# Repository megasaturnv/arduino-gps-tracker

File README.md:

# arduino-gps-tracker
## Synopsis
An Arduino-based GPS tracking solution. One Arduino and Ublox Neo-6m (GY-NEO6MV2) GPS module on stripboard / veroboard is used as the GPS tracking device. The other is an Arduino handheld controller which requests information from the tracking device and displays the coordinates, GPS location and location on a map. By default, the display is a 128x160 1.8" TFT LCD but the code can be adapted for other displays. Communication occurs between the two devices with the HC-12 wireless serial communication module. This project can be adapted to use other methods of wireless communication such as the XBee or GSM mobile network. Please make sure the frequency used and transmitting power is legal in your country.

## Description of Arduino handheld controller
The Arduino handheld controller is used by a user to find the location of their GPS tracking device. It is powered by an 18650 Li-ion cell and consists of Li-ion protection and charging circuitry, an Arduino, a 1.8" TFT LCD display, a HC-12 wireless communication module and buttons for requesting various data from the tracking device. When it receives data from the tracking device, the Arduino will interpret the message formtted as \<datatype>:\<CSV of data> into \<data type> and an array of data for each item in \<CSV of data>. Then, the tracker respond in the appropriate way. The messages it understands and the way it responds are listed below:

#### if receive "volts:\[millivolts\]"
Display the tracking device Arduino's VCC voltage on the 1.8" TFT LCD display.

#### if receive "gps:\<latitude>, \<longitude>, \<num of satellites>, \<accuracy>, \<speed>, \<direction>, \<age of data>, \<checksum>"
Display these figures on the 1.8" TFT LCD display.

### Buttons
The buttons on the handheld controller are pulled high by the Arduino's internal pull-up resistors. To activate the button, the pin should be connected to ground. 

### The Arduino pins used to connect to peripherals is shown below:
#define name | Pin no. | Function
--- | --- | ---
SOFTWARE_SERIAL_TX | 2 | For the HC-12 module. Connects to HC-12 RX
SOFTWARE_SERIAL_RX | 3 | For the HC-12 module. Connects to HC-12 TX
CELLVOLTS_BUTTON | 4 | Push button connected to ground. transmit: "cell:volts" to the tracking device
REQUEST_GPS_ONCE_BUTTON | 5 | Push button connected to ground. transmit: "gps:once"
REQUEST_GPS_CONTINUOUS_BUTTON | 6 | Push button connected to ground. transmit: "gps:continuous"
REQUEST_GPS_STOP_BUTTON | 7 | Push button connected to ground. transmit: "gps:stop"
sclk | 13 | Connection to 1.8" TFT LCD screen. Connects to TFT SCK/
mosi | 11 | Connection to 1.8" TFT LCD screen. Connects to TFT SDA/
cs | 10 | Connection to 1.8" TFT LCD screen. Connects to TFT SCS/
dc | A0 | Connection to 1.8" TFT LCD screen. Connects to TFT A0/
rst | A1 | Connection to 1.8" TFT LCD screen. Connects to TFT RESET/

### Showing location on the display's map
*COMING SOON*

### How to create your own maps for the TFT LCD screen
*COMING SOON*

## Description of Arduino GPS tracking device
The Arduino tracking device should be attached to an object which the user wants to track. It is powered by an 18650 Li-ion cell and consists of Li-ion protection and charging circuitry, an Arduino, a Ublox Neo-6m (GY-NEO6MV2) GPS module and a HC-12 wireless communication module. The circuit is built onto a piece of stripboard / veroboard. When powered, the Arduino will go into a light sleep mode. It will wake up when it receives serial data from the HC-12 module. The Arduino will interpret the message formtted as \<datatype>:\<CSV of data> into \<data type> and an array of data for each item in \<CSV of data>. Then, the tracker responds in the appropriate way.

### Kicad designs

### The messages the Arduino GPS tracking device understands and the way it responds are listed below:
#### if receive "cell:volts"
send "cell:\[millivolts\]" where millivolts = voltage of the tracking device Arduino's VCC pin

#### if receive "gps:once"
send "message:received gps once" and try to get GPS coordinates. Then, send coordinates once and go to sleep

#### if receive "gps:continuous"
send "message:received gps continuous" and try to get GPS coordinates. Then, send coordinates every 10 seconds

#### if receive "gps:stopcontinuous"
send "message:gpsstopcontinuous" and then stop sending GPS coordinates continuously

If the tracking device is requested for coordinates, it will try and get its GPS location. If it cannot get a fix after GPS_TIMEOUT milliseconds, the Arduino will send "message:Unable to get GPS fix" to the handheld controller, where it will be displayed on the screen. This functionality can be disabled by setting GPS_TIMEOUT to 0 (#define GPS_TIMEOUT 0).

If no more GPS coordinates are required (after a successful GPS lock with "gps:once" or "gps:stopcontinuous" commmand) or if the Arduino has been on for more than MAX_ON_TIME, go to sleep. MAX_ON_TIME is a failsafe to make sure the Arduino doesn't stay on for more than MAX_ON_TIME milliseconds. This functionality can be disabled by setting MAX_ON_TIME to 0 (#define MAX_ON_TIME 0).

### The Arduino pins used to connect to peripherals is shown below:

Pin description | Pin no. | Function
--- | --- | ---
SERIAL_UART_RX | 0 | For the HC-12 module. Connects to HC-12 TX
SERIAL_UART_TX | 1 | For the HC-12 module. Connects to HC-12 RX

#define name | Pin no. | Function
--- | --- | ---
SOFTWARE_SERIAL_RX | 3 | Software serial RX pin, to be connected to the GPS module's TX
SOFTWARE_SERIAL_TX | 2 | Software serial TX pin, to be connected to the GPS module's RX

## Motivation
I have created this project to be used as a dog tracker, but it can easily track a car and other valuable item.

## Installation
Upload gpsTracker_handheldController to the Arduino which will be used in the handheld controller. Upload gpsTracker_trackingDevice to the Arduino which will be used in the tracking device. Follow the build diagrams and create the stripboard / veroboard circuit board from the KiCAD files to construct the GPS tracking device.

## Libraries used
### Handheld controller
* [Adafruit_GFX](https://github.com/adafruit/Adafruit-GFX-Library)
* [Adafruit_QDTech](https://github.com/zigwart/Adafruit_QDTech) Note my display is QDTech 1.8" 128x160 pixel LCD board using a Samsung S6D02A1 chip, so I need a special library.
* [SPI](https://github.com/arduino/Arduino/tree/master/hardware/arduino/avr/libraries/SPI)
* [SoftwareSerial](https://github.com/arduino/Arduino/tree/master/hardware/arduino/avr/libraries/SoftwareSerial)

### Tracking device
* [avr/power](https://github.com/Synapseware/avr/blob/master/include/avr/power.h)
* [avr/sleep](https://github.com/Synapseware/avr/blob/master/include/avr/sleep.h)
* [SoftwareSerial](https://github.com/arduino/Arduino/tree/master/hardware/arduino/avr/libraries/SoftwareSerial)
* [TinyGPS](http://arduiniana.org/libraries/tinygps/)

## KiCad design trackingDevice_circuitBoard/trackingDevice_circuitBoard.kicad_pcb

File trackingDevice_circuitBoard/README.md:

# gpsTracker_trackingDevice_circuitBoard
Schematic and circuit board design for the tracking device. Used to create a stripboard / veroboard circuit board.

To be opened with KiCad EDA, a cross platform, free and open source electronics design automation suite.
* http://kicad-pcb.org/
* https://github.com/kicad

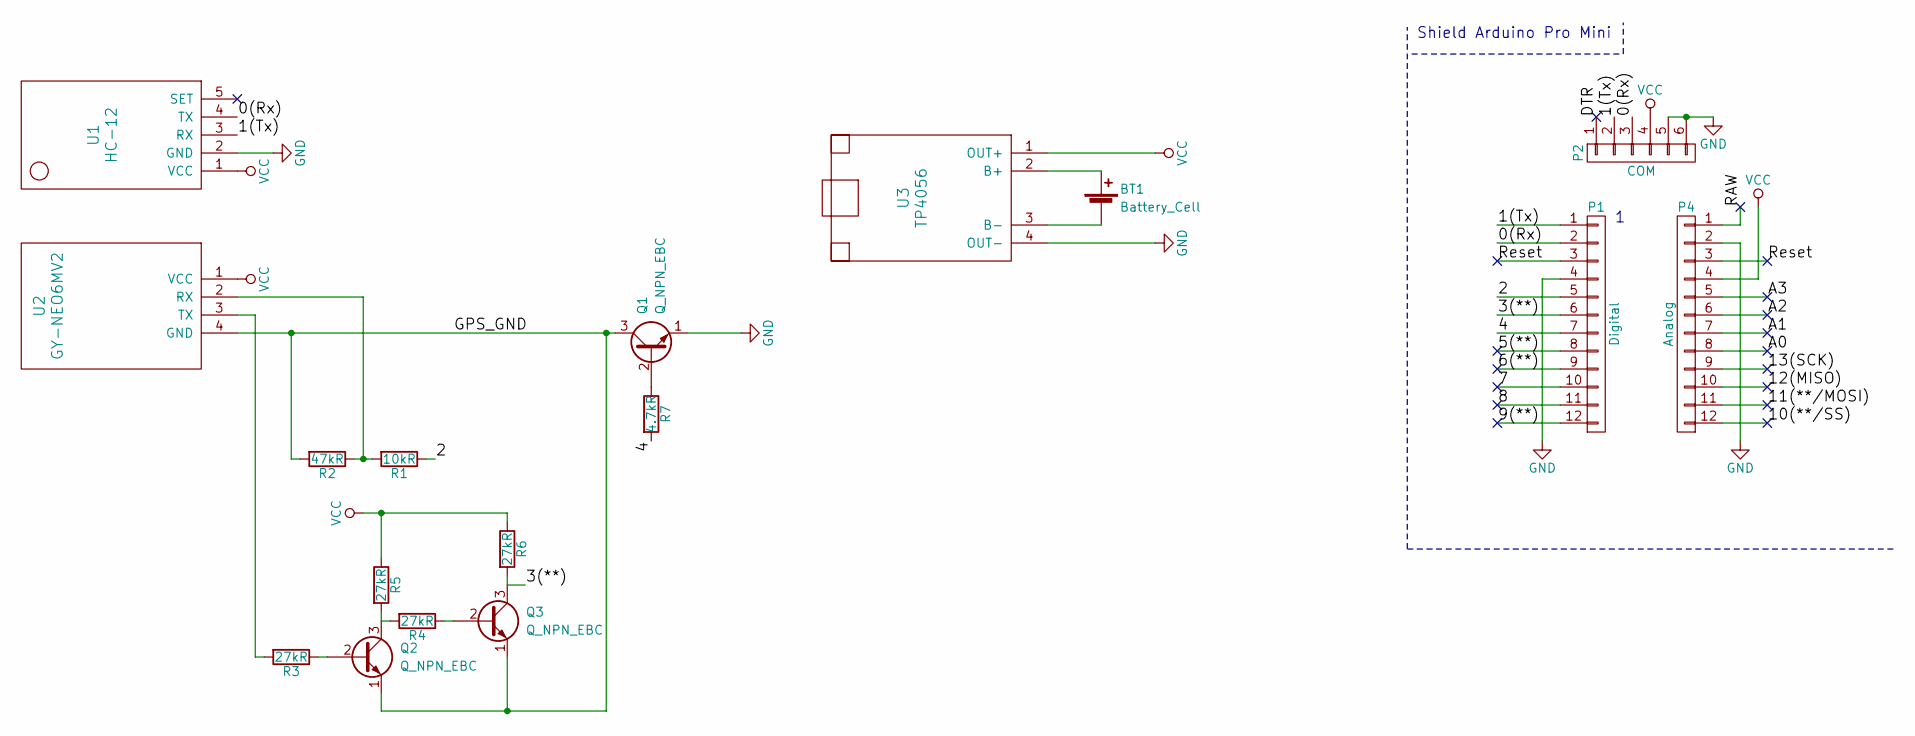
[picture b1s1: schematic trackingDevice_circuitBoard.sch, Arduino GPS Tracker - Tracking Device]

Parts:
BT1: Battery_Cell; CP_Axial_L67.0mm_D23.0mm_P75.00mm_Horizontal
P1: Digital; Socket_Strip_Straight_1x12_Pitch2.54mm
P2: COM
P4: Analog; Socket_Strip_Straight_1x12_Pitch2.54mm
Q1, Q2, Q3: Q_NPN_EBC; TO-92_Inline_Wide
R1: 10kR; R_Axial_DIN0207_L6.3mm_D2.5mm_P10.16mm_Horizontal
R2: 47kR; R_Axial_DIN0207_L6.3mm_D2.5mm_P10.16mm_Horizontal
R3, R4, R5, R6: 27kR; R_Axial_DIN0207_L6.3mm_D2.5mm_P10.16mm_Horizontal
R7: 4.7kR; R_Axial_DIN0207_L6.3mm_D2.5mm_P15.24mm_Horizontal
U1: HC-12; Socket_Strip_Straight_1x05_Pitch2.54mm
U2: GY-NEO6MV2; Socket_Strip_Straight_1x04_Pitch2.54mm
U3: TP4056; TP4056_with_protection

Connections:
/0(Rx): P1.2, P2.3, U1.4 (TX)
/1(Tx): P1.1, P2.2, U1.3 (RX)
/2: P1.5, R1.1
/3(**): P1.6, Q3.3 (C), R6.2
/4: P1.7, R7.2
/5(**): P1.8
/6(**): P1.9
/7: P1.10
/8: P1.11
/9(**): P1.12
/10(**/SS): P4.12
/11(**/MOSI): P4.11
/12(MISO): P4.10
/13(SCK): P4.9
/A0: P4.8
/A1: P4.7
/A2: P4.6
/A3: P4.5
/GPS_GND: Q1.3 (C), Q2.1 (E), Q3.1 (E), R2.2, U2.4 (GND)
/RAW: P4.1
/Reset: P1.3, P4.3
GND: P1.4, P2.5, P2.6, P4.2, Q1.1 (E), U1.2 (GND), U3.4 (OUT-)
unnamed: BT1.1 (+), U3.2 (B+)
unnamed: BT1.2 (-), U3.3 (B-)
unnamed: Q1.2 (B), R7.1
unnamed: Q2.2 (B), R3.1
unnamed: Q2.3 (C), R4.2, R5.2
unnamed: Q3.2 (B), R4.1
unnamed: R1.2, R2.1, U2.2 (RX)
unnamed: R3.2, U2.3 (TX)
VCC: P2.4, P4.4, R5.1, R6.1, U1.1 (VCC), U2.1 (VCC), U3.1 (OUT+)

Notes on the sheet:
Shield Arduino Pro Mini

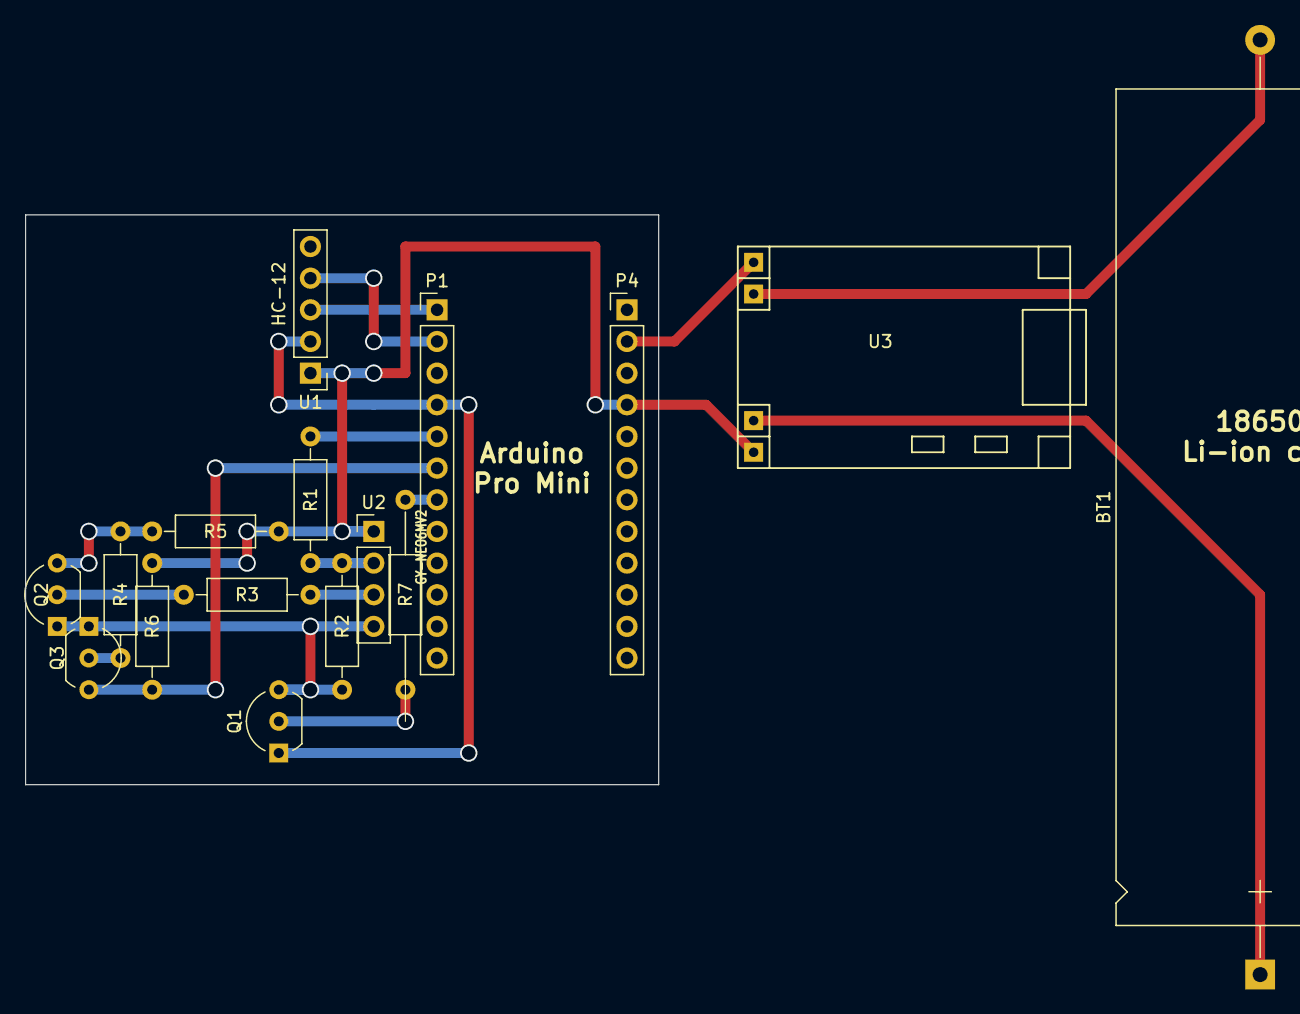
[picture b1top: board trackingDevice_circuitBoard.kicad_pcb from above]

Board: 2 copper layers, 50.8 x 45.7 mm, 16 parts (0 on the bottom side), 17 nets.

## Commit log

2017-05-25 Update README.md
    Added longer description
2017-05-26 Added handheld controller, tracking device and more
2017-05-26 Added tracking device files
2017-05-26 Added handheld controller files
2017-05-26 v0.1 changelog
2017-05-26 Added maps in separate folder
2017-05-27 Initial changes
2017-05-30 Updated to v0.2
2017-05-30 Added ability to show the current location on the map
2017-05-30 Fine tuned delay values and commented out some debugging code
2017-05-30 Updated to v0.2.1
2017-05-30 Added clear map button on pin 8
2017-06-04 Updated to v0.3
2017-06-04 Increased default MAX_ON_TIME to 1 hour
2017-06-04 Updated to v0.3. Added location history and arrows when tracker is outside the map's area
2017-06-04 Added test code for drawing arrows on the screen
2017-06-04 Updated to v0.3.1
2017-06-04 Added more configuration constants
2017-06-04 Added circuit board files for the tracking device
    For use with KiCad
2017-06-04 Updated to v0.3.2
2017-06-05 Bugfixes, added more configuration constants and code comments
2017-06-05 Updated to v0.3.3
2017-06-05 Added ability to control GPS module's power through a MOSFET
2017-06-05 Updated to v0.3.4
2017-06-11 Updated to v0.4
2017-06-11 Changed items shown on TFT screen and it can now read the Vcc voltage
2017-06-11 Added ability to read own Vcc input voltage
2017-06-24 Renamed files and folders
2017-06-24 Updated to v0.4.1
2018-02-14 Create LICENSE
2018-06-09 Corrected typo
2018-06-09 Replaced ping feature with reading the tracking device Arduino's VCC voltage
2018-06-09 Fixed discontinuity bug with gps:stop
    gps:stopcontinuous changed to gps:stop for tracking device code. Initially the tracking device was listening for the wrong stop message from the handheld controller.
2018-06-09 Update comments. No code changes
2018-06-09 Corrected Arduino tracking device pin functions
2018-06-10 Added breadboard pictures #2
2018-06-10 Added tracking device circuit board and schematic pictures #2
2018-06-10 Replaced MOSFET with NPN transistor and changed package to TO-126
2018-06-10 Added images to README #2
2018-06-10 Added image of screen showing the location marker #2
2018-06-10 Removed old map and added steps for creating xbm map file
2018-06-13 Moved circuit board SVGs
2018-07-18 Corrected error in tracking device circuit
2018-08-09 Added veroboard/stripboard drill marks + corrected error in tracking device circuit
2018-08-09 Updated to mention stripboard / veroboard
2018-08-09 Updated to mention stripboard / veroboard (2)
2018-08-13 Modified resistor values to be more power-efficient
2018-08-26 Added remote programming of the HC-12 module
